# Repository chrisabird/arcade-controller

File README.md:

# USB MAME Arcade Controller

The ATMega328 source code for the USB MAME arcade controller.

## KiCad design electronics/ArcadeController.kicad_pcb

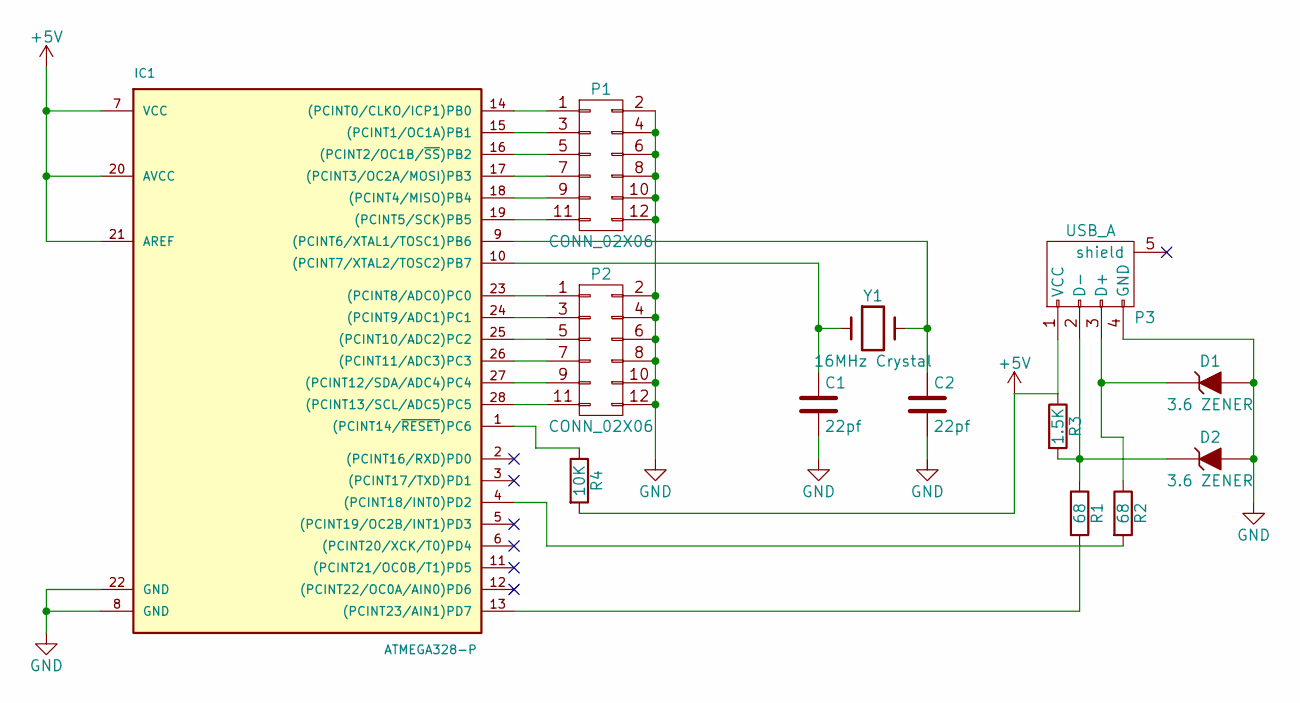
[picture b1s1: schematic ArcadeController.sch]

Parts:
C1, C2: 22pf; C_Disc_D3_P2.5
D1, D2: 3.6 ZENER; Diode_DO-35_SOD27_Horizontal_RM10
IC1: ATMEGA328-P; DIP-28_W7.62mm_LongPads
P1, P2: CONN_02X06; Socket_Strip_Straight_2x06
P3: USB_A; USB_B
R1, R2: 68; Resistor_Horizontal_RM10mm
R3: 1.5K; Resistor_Horizontal_RM10mm
R4: 10K; Resistor_Horizontal_RM10mm
Y1: 16MHz Crystal; HC-49V

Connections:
+5V: IC1.7 (VCC), IC1.20 (AVCC), IC1.21 (AREF), P3.1 (VCC), R3.1, R4.2
GND: C1.2, C2.2, D1.2 (A), D2.2 (A), IC1.8 (GND), IC1.22 (GND), P1.2, P1.4, P1.6, P1.8, P1.10, P1.12, P2.2, P2.4, P2.6, P2.8, P2.10, P2.12, P3.4 (GND)
unnamed: C1.1, IC1.10 ((PCINT7/XTAL2/TOSC2)PB7), Y1.1
unnamed: C2.1, IC1.9 ((PCINT6/XTAL1/TOSC1)PB6), Y1.2
unnamed: D1.1 (K), P3.3 (D+), R2.1
unnamed: D2.1 (K), P3.2 (D-), R1.1, R3.2
unnamed: IC1.1 ((PCINT14/~RESET~)PC6), R4.1
unnamed: IC1.4 ((PCINT18/INT0)PD2), R2.2
unnamed: IC1.13 ((PCINT23/AIN1)PD7), R1.2
unnamed: IC1.14 ((PCINT0/CLKO/ICP1)PB0), P1.1
unnamed: IC1.15 ((PCINT1/OC1A)PB1), P1.3
unnamed: IC1.16 ((PCINT2/OC1B/~SS~)PB2), P1.5
unnamed: IC1.17 ((PCINT3/OC2A/MOSI)PB3), P1.7
unnamed: IC1.18 ((PCINT4/MISO)PB4), P1.9
unnamed: IC1.19 ((PCINT5/SCK)PB5), P1.11
unnamed: IC1.23 ((PCINT8/ADC0)PC0), P2.1
unnamed: IC1.24 ((PCINT9/ADC1)PC1), P2.3
unnamed: IC1.25 ((PCINT10/ADC2)PC2), P2.5
unnamed: IC1.26 ((PCINT11/ADC3)PC3), P2.7
unnamed: IC1.27 ((PCINT12/SDA/ADC4)PC4), P2.9
unnamed: IC1.28 ((PCINT13/SCL/ADC5)PC5), P2.11

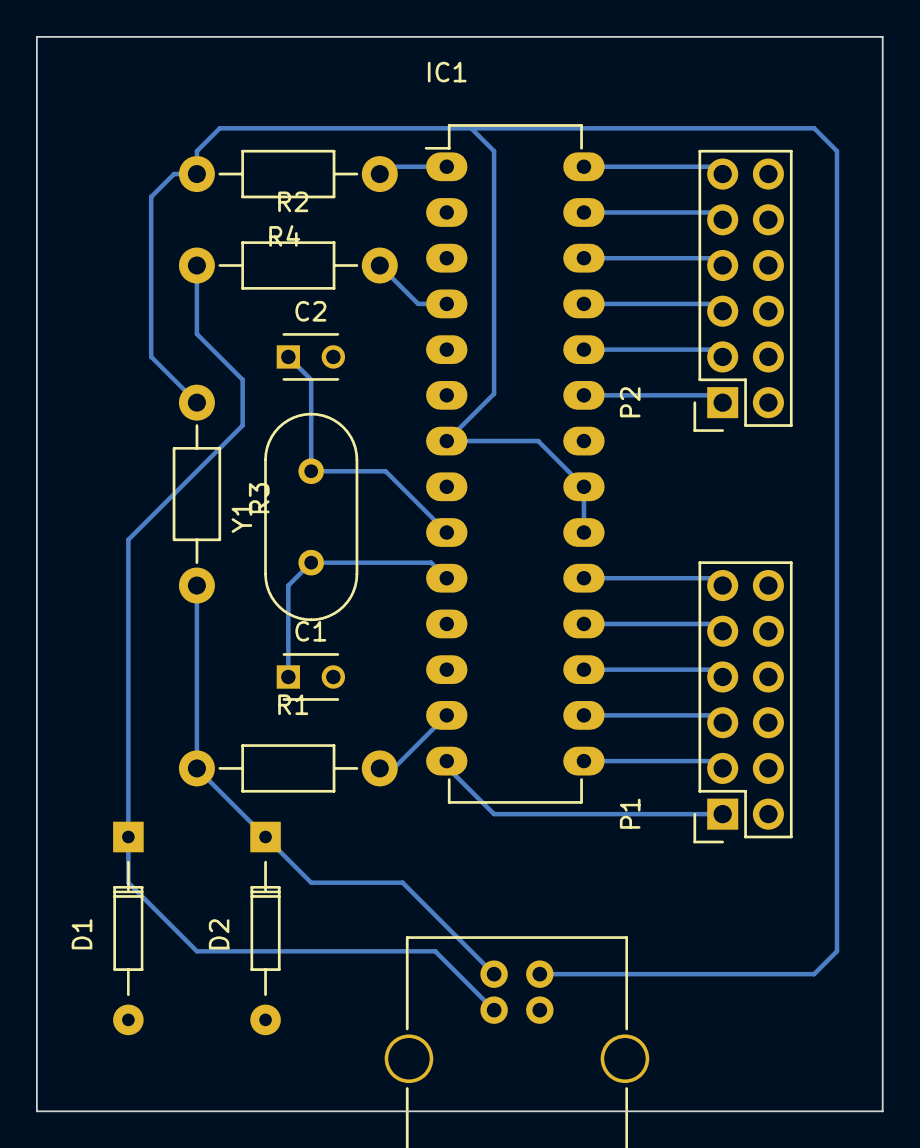
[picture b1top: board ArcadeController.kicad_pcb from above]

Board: 2 copper layers, 47.0 x 59.7 mm, 13 parts (0 on the bottom side), 21 nets.

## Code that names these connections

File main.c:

#include <avr/io.h>
#include <avr/wdt.h>
#include "usbdrv/usbconfig.h"
#include "usbdrv/usbdrv.h"
#include <avr/pgmspace.h>
#include <avr/interrupt.h>
#include <avr/power.h>
#include <util/delay.h>

#define REPORT_BUFFER_FULL_SIZE 8
#define REPORT_BUFFER_SIZE 6
#define KEYPRESS_BUFFER_SIZE 6

uint8_t report_buffer[REPORT_BUFFER_FULL_SIZE];
uint8_t usb_hasCommed = 0;
uint8_t idle_rate = 500 / 4;
uint8_t protocol_version = 0;
uint8_t led_state = 0;

uint8_t keypress_buffer[KEYPRESS_BUFFER_SIZE] = {};
uint8_t keypress_buffer_counter = 0;

uint8_t read_state = 0;
uint16_t read_wait_counter = 0;

void usbBegin()
{
    PORTD &= ~(_BV(USB_CFG_DMINUS_BIT) | _BV(USB_CFG_DPLUS_BIT));

    usbDeviceDisconnect();
    _delay_ms(300);
    usbDeviceConnect();

    wdt_enable(WDTO_1S);
    usbInit();
}

const PROGMEM char usbHidReportDescriptor[USB_CFG_HID_REPORT_DESCRIPTOR_LENGTH] = {
	0x05, 0x01,  // USAGE_PAGE (Generic Desktop)
	0x09, 0x06,  // USAGE (Keyboard)
	0xA1, 0x01,  // COLLECTION (Application)
	0x05, 0x07,  //   USAGE_PAGE (Keyboard)(Key Codes)
	0x19, 0xE0,  //   USAGE_MINIMUM (Keyboard LeftControl)(224)
	0x29, 0xE7,  //   USAGE_MAXIMUM (Keyboard Right GUI)(231)
	0x15, 0x00,  //   LOGICAL_MINIMUM (0)
	0x25, 0x01,  //   LOGICAL_MAXIMUM (1)
	0x75, 0x01,  //   REPORT_SIZE (1)
	0x95, 0x08,  //   REPORT_COUNT (8)
	0x81, 0x02,  //   INPUT (Data,Var,Abs) ; Modifier byte
	0x95, 0x01,  //   REPORT_COUNT (1)
	0x75, 0x08,  //   REPORT_SIZE (8)
	0x81, 0x03,  //   INPUT (Cnst,Var,Abs) ; Reserved byte
	0x95, 0x05,  //   REPORT_COUNT (5)
	0x75, 0x01,  //   REPORT_SIZE (1)
	0x05, 0x08,  //   USAGE_PAGE (LEDs)
	0x19, 0x01,  //   USAGE_MINIMUM (Num Lock)
	0x29, 0x05,  //   USAGE_MAXIMUM (Kana)
	0x91, 0x02,  //   OUTPUT (Data,Var,Abs) ; LED report
	0x95, 0x01,  //   REPORT_COUNT (1)
	0x75, 0x03,  //   REPORT_SIZE (3)
	0x91, 0x03,  //   OUTPUT (Cnst,Var,Abs) ; LED report padding
	0x95, 0x06,  //   REPORT_COUNT (6)
	0x75, 0x08,  //   REPORT_SIZE (8)
	0x15, 0x00,  //   LOGICAL_MINIMUM (0)
	0x25, 0x65,  //   LOGICAL_MAXIMUM (101)
	0x05, 0x07,  //   USAGE_PAGE (Keyboard)(Key Codes)
	0x19, 0x00,  //   USAGE_MINIMUM (Reserved (no evFAent indicated))(0)
	0x29, 0x65,  //   USAGE_MAXIMUM (Keyboard Application)(101)
	0x81, 0x00,  //   INPUT (Data,Ary,Abs)
	0xC0         // END_COLLECTION
};

usbMsgLen_t usbFunctionSetup(uint8_t data[8])
{
	usb_hasCommed = 1;

	// see HID1_11.pdf sect 7.2 and http://vusb.wikidot.com/driver-api
	usbRequest_t *rq = (void *)data;

	if ((rq->bmRequestType & USBRQ_TYPE_MASK) != USBRQ_TYPE_CLASS)
		return 0; // ignore request if it's not a class specific request

	// see HID1_11.pdf sect 7.2
	switch (rq->bRequest)
	{
		case USBRQ_HID_GET_IDLE:
			usbMsgPtr = &idle_rate; // send data starting from this byte
			return 1; // send 1 byte
		case USBRQ_HID_SET_IDLE:
			idle_rate = rq->wValue.bytes[1]; // read in idle rate
			return 0; // send nothing
		case USBRQ_HID_GET_PROTOCOL:
			usbMsgPtr = &protocol_version; // send data starting from this byte
			return 1; // send 1 byte
		case USBRQ_HID_SET_PROTOCOL:
			protocol_version = rq->wValue.bytes[1];
			return 0; // send nothing
		case USBRQ_HID_GET_REPORT:
			usbMsgPtr = (uint8_t*)report_buffer; // send the report data
			return 8;
		case USBRQ_HID_SET_REPORT:
			if (rq->wLength.word == 1) // check data is available
			{
				return USB_NO_MSG; // send nothing but call usbFunctionWrite
			}
			else // no data or do not understandFAFU2EHA data, ignore
			{
				return 0; // send nothing
			}
		default: // do not understand data, ignore
			return 0; // send nothing
	}
}

usbMsgLen_t usbFunctionWrite(uint8_t * data, uchar len)
{
	led_state = data[0];
	return 1; // 1 byte read
}

// Start    - 1       - 1E  - 30    - PB0
// Coin     - 5       - 22  - 34    - PB1
// Fire1    - L Ctrl  - E0  - 224   - PB2
// Fire2    - L Alt   - E2  - 226   - PB3
// Fire3    - Space   - 2C  - 44    - PB4
// Fire4    - L Shift - E1  - 225   - PB5
int portBKeyMap[6] = {0x1E, 0x22, 0xE0, 0xE2, 0x2c, 0xE1};

// Fire5    - Z       - 1D  - 29    - PC0
// Fire6    - X       - 1B  - 27    - PC1
// Up       - Up      - 52  - 82    - PC2
// Down     - Down    - 51  - 81    - PC3
// Left     - Left    - 50  - 80    - PC4
// Right    - Right   - 4F  - 79    - PC5
int portCKeyMap[6] = {0x1D, 0x1B, 0x52, 0x51, 0x50, 0x4F};

void readKeys() {
  uint8_t keyNumber = 0;
  uint8_t i = 0;
  for(i = 0; i < KEYPRESS_BUFFER_SIZE; i++) {
    keypress_buffer[i] = 0;
  }
  keypress_buffer_counter = 0;

  for(keyNumber = 0 ; keyNumber < 6; keyNumber++) {
    if(keypress_buffer_counter >= KEYPRESS_BUFFER_SIZE) {
      break;
    }

    if(!(PINB & (1<<keyNumber))) {
      uint8_t key = portBKeyMap[keyNumber];
      keypress_buffer[keypress_buffer_counter++] = key;
    }
  }

  for(keyNumber = 0 ; keyNumber < 5; keyNumber++) {
    if(keypress_buffer_counter >= KEYPRESS_BUFFER_SIZE) {
      break;
    }

    if(!(PINC & (1<<keyNumber))) {
      uint8_t key = portCKeyMap[keyNumber];
      keypress_buffer[keypress_buffer_counter++] = key;
    }
  }
}

void buildReport() {
  report_buffer[0] = 0;
  report_buffer[1] = 0;
  uint8_t i = 0;
  for(i = 0; i < KEYPRESS_BUFFER_SIZE; i++) {
    report_buffer[i+2] = keypress_buffer[i];
  }
}

void setupPorts() {
  DDRB = 0b00000000; // Port B 0-5 for Input 6-7 Reserved for XTAL
  PORTB = 0b00011111;
  DDRC = 0b00000000; // Port C 0-5 for Input 6 Unused
  PORTC = 0b00011111;
  PORTD = 0xfa;   // 1111 1010 bin: activate pull-ups except on USB lines */
  DDRD = 0x07;    // 0000 0111 bin: all pins input except USB (-> USB reset) */
  _delay_ms(20);
  DDRD = 0x00;    // 0000 0000 bin: remove USB reset condition
  TCCR0B = 5;      // Timer0 prescaler: 1024
}

int main(void) {

  cli();
  setupPorts();
  usbBegin();
  sei();

  for (;;) {
    wdt_reset();
    usbPoll();

    if(read_state == 0) {
      readKeys();
      read_state = 1;
    } else {
      if(read_wait_counter == 0x1000) {
        read_wait_counter++;
        read_wait_counter = 0;
        read_state = 0;
      } else {
        read_wait_counter++;
      }
    }

		if (usbInterruptIsReady())
		{
      buildReport();
      usbSetInterrupt((uint8_t*)report_buffer, REPORT_BUFFER_FULL_SIZE); // send
		}
  }
  return 0;
}

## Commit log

2015-10-24 Renamed readme
2015-10-24 Adding readme content
2015-10-24 Make readme markdown
2015-10-24 Added schematics, pcb layout
